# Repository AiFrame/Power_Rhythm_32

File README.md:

Power_Rhythm_32
===============

32 channels servo controller source code

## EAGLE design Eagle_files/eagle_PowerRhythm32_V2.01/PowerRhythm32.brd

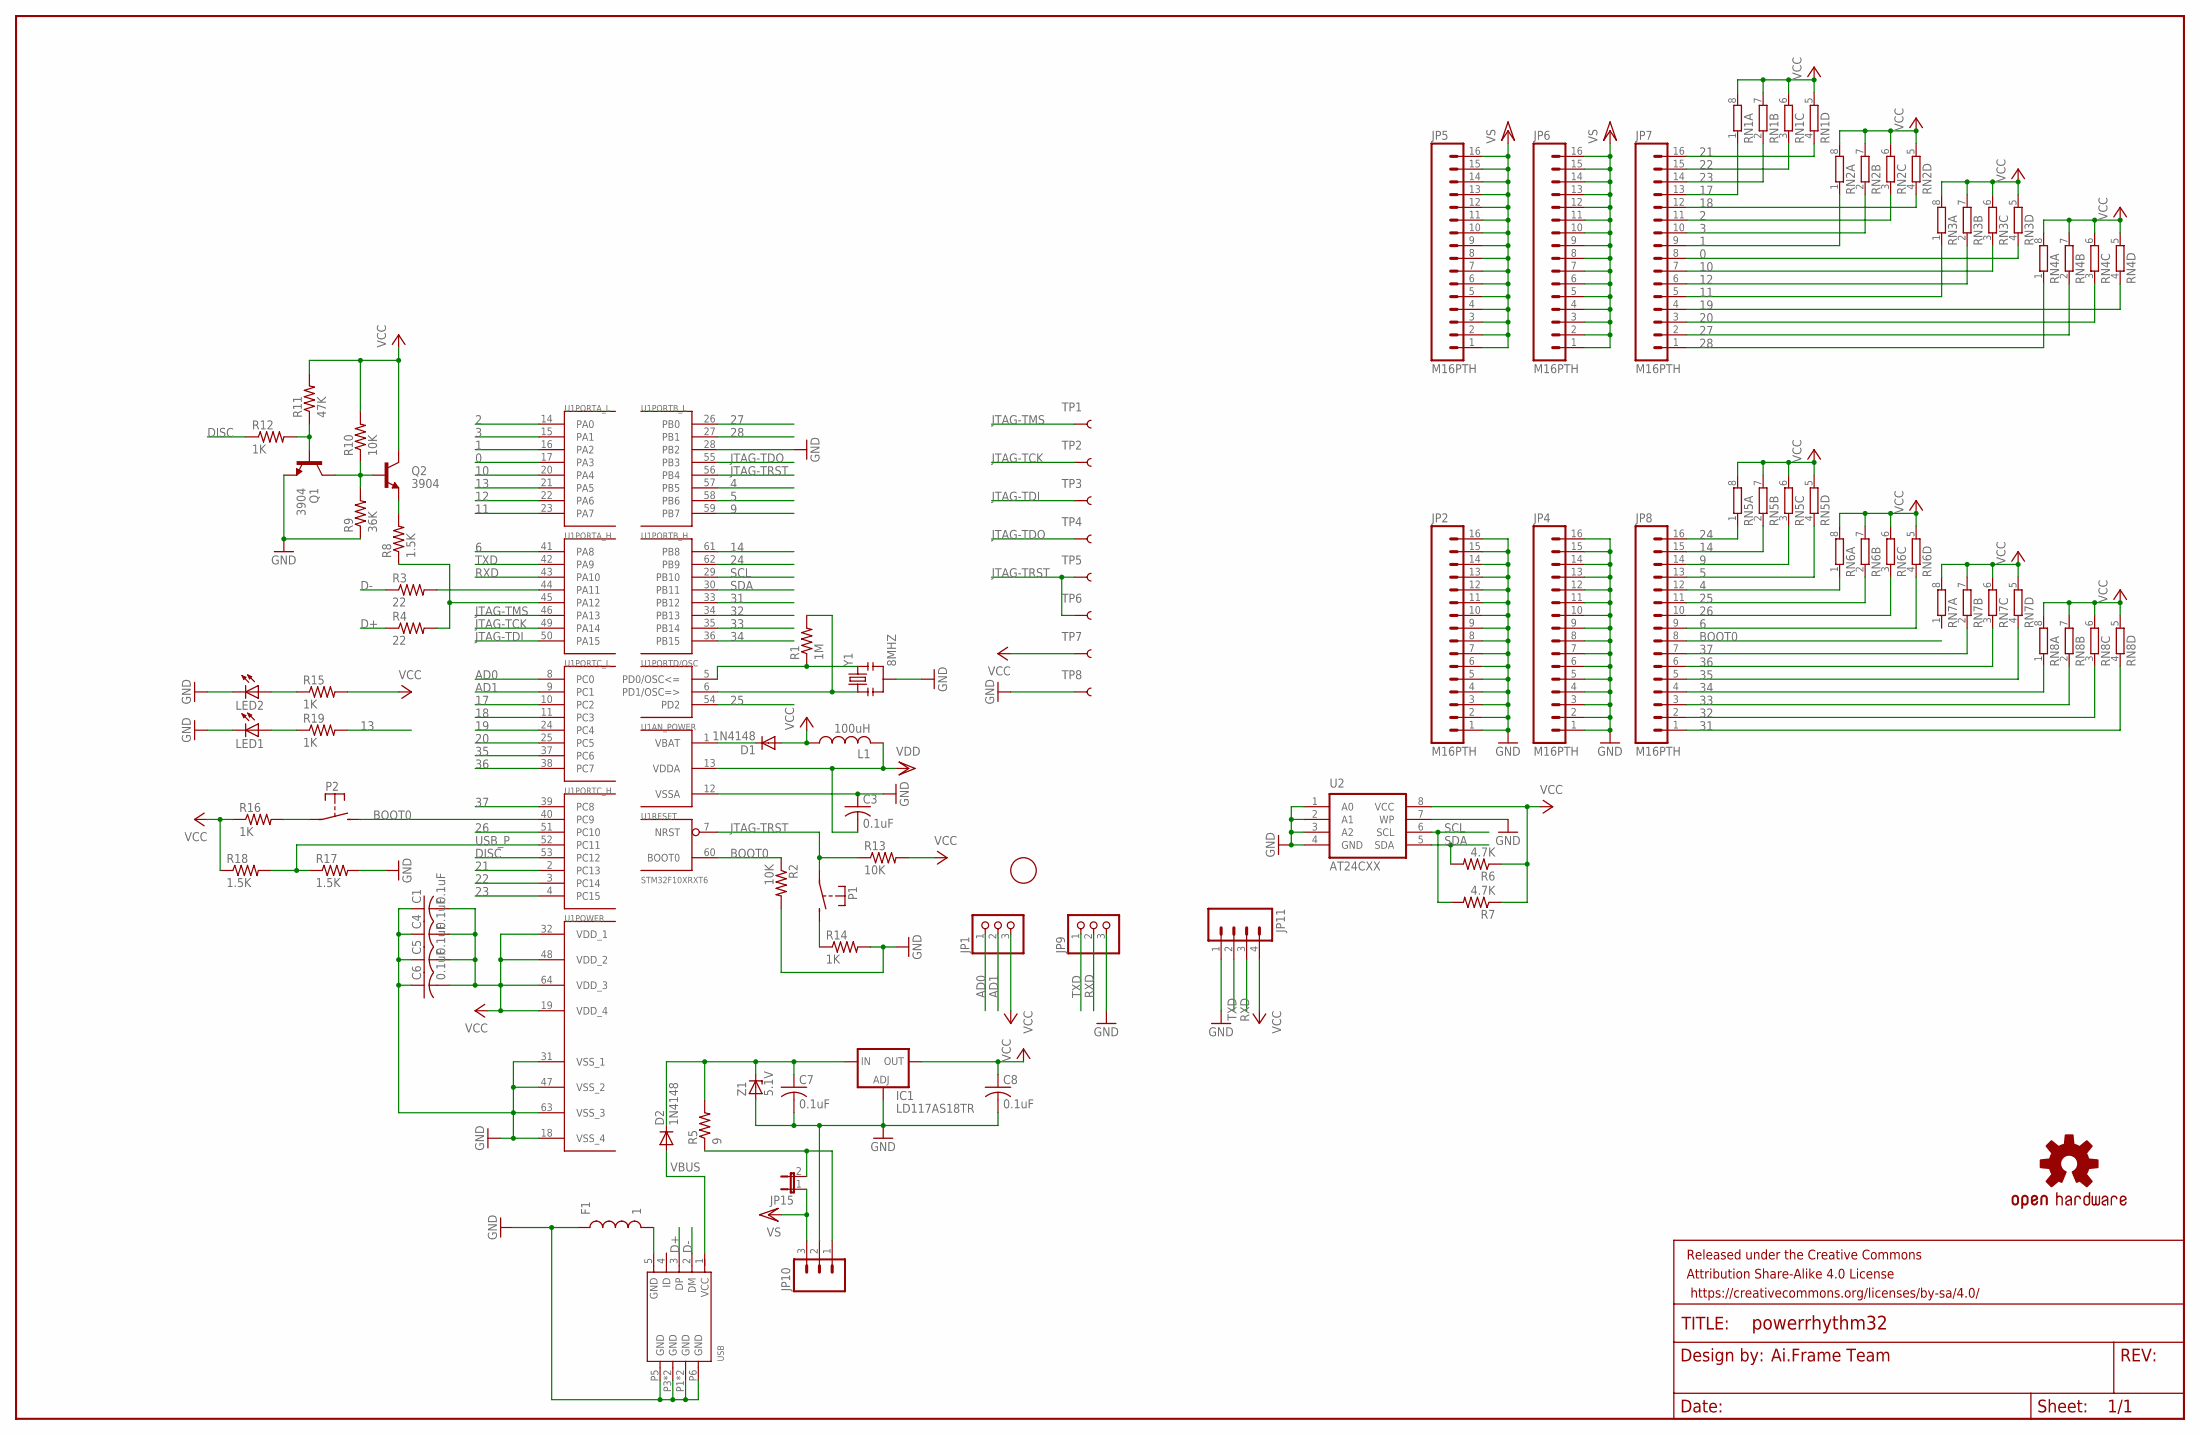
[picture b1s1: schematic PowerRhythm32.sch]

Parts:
C1, C3, C4, C5, C6, C7, C8: 0.1uF; C0603K
D1, D2: 1N4148; SOD123
F1: 1; 0805
FRAME1: FRAME-LEDGER; CREATIVE_COMMONS
IC1: LD117AS18TR; SOT223
JP1, JP9: PINHD-1X3; 1X03
JP2, JP4, JP5, JP6, JP7, JP8: M16PTH; 1X16
JP10: M03SCREW_LOCK; SCREWTERMINAL-3.5MM-3_LOCK.007S
JP11: M04PTH; 1X04
JP15: JUMPER-2PTH; 1X02
L1: 100uH; L2012C
LED1, LED2: LEDCHIP-LED0603; CHIP-LED0603
LOGO1: OSHW-LOGOS; OSHW-LOGO-S
P1, P2: TMAV433BAA
Q1, Q2: 3904; SOT23-3
R1: 1M; R0603
R2, R10, R13: 10K; R0603
R3, R4: 22; R0603
R5: 9; R1206
R6, R7: 4.7K; R0603
R8, R17, R18: 1.5K; R0603
R9: 36K; R0603
R11: 47K; R0603
R12, R14, R15, R16, R19: 1K; R0603
RN1, RN2, RN3, RN4, RN5, RN6, RN7, RN8: 4R-N0603-ARC; 0603-ARC
TP1, TP2, TP3, TP4, TP5, TP6, TP7, TP8: TEST-POINT3X5; PAD.03X.05
U1: STM32F10XRXT6; TQFP64
U2: AT24CXX; SO08-8S1
U$1: FIDUCIAL; FIDUCIAL_1MM
USB: MICRO-USB5+4P'5+6P'; MICRO-USB5+6P-SMD-0.65-AB
Y1: 8MHZ; RESONATOR-SMD
Z1: 5.1V; SOD80C

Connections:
0: JP7.8, RN3.4 (1), U1.17 (PA3)
1: JP7.9, RN2.1, U1.16 (PA2)
2: JP7.11, RN2.3 (1), U1.14 (PA0)
3: JP7.10, RN2.2 (1), U1.15 (PA1)
4: JP8.12, RN6.1, U1.57 (PB5)
5: JP8.13, RN5.4 (1), U1.58 (PB6)
6: JP8.9, RN6.4 (1), U1.41 (PA8)
9: JP8.14, RN5.3 (1), U1.59 (PB7)
10: JP7.7, RN3.3 (1), U1.20 (PA4)
11: JP7.5, RN3.1, U1.23 (PA7)
12: JP7.6, RN3.2 (1), U1.22 (PA6)
13: R19.2, U1.21 (PA5)
14: JP8.15, RN5.2 (1), U1.61 (PB8)
17: JP7.13, RN1.1, U1.10 (PC2)
18: JP7.12, RN2.4 (1), U1.11 (PC3)
19: JP7.4, RN4.4 (1), U1.24 (PC4)
20: JP7.3, RN4.3 (1), U1.25 (PC5)
21: JP7.16, RN1.4 (1), U1.2 (PC13)
22: JP7.15, RN1.3 (1), U1.3 (PC14)
23: JP7.14, RN1.2 (1), U1.4 (PC15)
24: JP8.16, RN5.1, U1.62 (PB9)
25: JP8.11, RN6.2 (1), U1.54 (PD2)
26: JP8.10, RN6.3 (1), U1.51 (PC10)
27: JP7.2, RN4.2 (1), U1.26 (PB0)
28: JP7.1, RN4.1, U1.27 (PB1)
31: JP8.1, RN8.4 (1), U1.33 (PB12)
32: JP8.2, RN8.3 (1), U1.34 (PB13)
33: JP8.3, RN8.2 (1), U1.35 (PB14)
34: JP8.4, RN8.1, U1.36 (PB15)
35: JP8.5, RN7.4 (1), U1.37 (PC6)
36: JP8.6, RN7.3 (1), U1.38 (PC7)
37: JP8.7, RN7.2 (1), U1.39 (PC8)
AD0: JP1.1, U1.8 (PC0)
AD1: JP1.2, U1.9 (PC1)
BOOT0: JP8.8, P2.P$2 (S), R2.1, U1.40 (PC9), U1.60 (BOOT0)
D+: R4.1, USB.3 (DP)
D-: R3.1, USB.2 (DM)
DISC: R12.1, U1.53 (PC12)
GND: C1.1, C3.1, C4.1, C5.1, C6.1, C7.2, C8.2, F1.1, IC1.1 (ADJ), JP2.1, JP2.2, JP2.3, JP2.4, JP2.5, JP2.6, JP2.7, JP2.8, JP2.9, JP2.10, JP2.11, JP2.12, JP2.13, JP2.14, JP2.15, JP2.16, JP4.1, JP4.2, JP4.3, JP4.4, JP4.5, JP4.6, JP4.7, JP4.8, JP4.9, JP4.10, JP4.11, JP4.12, JP4.13, JP4.14, JP4.15, JP4.16, JP9.3, JP10.2, JP11.1, LED1.C, LED2.C, Q1.2 (E), R2.2, R9.1, R14.2, R17.2, TP8.P$1, U1.12 (VSSA), U1.18 (VSS_4), U1.28 (PB2), U1.31 (VSS_1), U1.47 (VSS_2), U1.63 (VSS_3), U2.1 (A0), U2.2 (A1), U2.3 (A2), U2.4 (GND), U2.7 (WP), USB.P1 (GND), USB.P2 (GND), USB.P3 (GND), USB.P4 (GND), USB.P5 (GND), USB.P6 (GND), Y1.2, Z1.A
JTAG-TCK: TP2.P$1, U1.49 (PA14)
JTAG-TDI: TP3.P$1, U1.50 (PA15)
JTAG-TDO: TP4.P$1, U1.55 (PB3)
JTAG-TMS: TP1.P$1, U1.46 (PA13)
JTAG-TRST: P1.P$1, R13.1, TP5.P$1, TP6.P$1, U1.7 (NRST), U1.56 (PB4)
unnamed: R1.2, U1.6 (PD1/OSC=>), Y1.1
unnamed: D1.C, U1.1 (VBAT)
unnamed: LED2.A, R15.1
unnamed: R4.2, R8.1, U1.45 (PA12)
unnamed: JP10.1, JP15.2, R5.1
unnamed: R1.1, U1.5 (PD0/OSC<=), Y1.3
unnamed: R3.2, U1.44 (PA11)
unnamed: C7.1, D2.C, IC1.3 (IN), R5.2, Z1.C
unnamed: LED1.A, R19.1
unnamed: F1.2, USB.5 (GND)
unnamed: Q1.3 (C), Q2.1 (B), R9.2, R10.1
unnamed: P1.P$2 (S), R14.1
unnamed: Q2.2 (E), R8.2
unnamed: Q1.1 (B), R11.1, R12.2
unnamed: P2.P$1, R16.2
RXD: JP9.2, JP11.3, U1.43 (PA10)
SCL: R7.2, U1.29 (PB10), U2.6 (SCL)
SDA: R6.2, U1.30 (PB11), U2.5 (SDA)
TXD: JP9.1, JP11.2, U1.42 (PA9)
USB_P: R17.1, R18.2, U1.52 (PC11)
VBUS: D2.A, USB.1 (VCC)
VCC: C1.2, C4.2, C5.2, C6.2, C8.1, D1.A, IC1.4 (OUT), JP1.3, JP11.4, L1.1, Q2.3 (C), R6.1, R7.1, R10.2, R11.2, R13.2, R15.2, R16.1, R18.1, RN1.5 (2), RN1.6 (2), RN1.7 (2), RN1.8 (2), RN2.5 (2), RN2.6 (2), RN2.7 (2), RN2.8 (2), RN3.5 (2), RN3.6 (2), RN3.7 (2), RN3.8 (2), RN4.5 (2), RN4.6 (2), RN4.7 (2), RN4.8 (2), RN5.5 (2), RN5.6 (2), RN5.7 (2), RN5.8 (2), RN6.5 (2), RN6.6 (2), RN6.7 (2), RN6.8 (2), RN7.5 (2), RN7.6 (2), RN7.7 (2), RN7.8 (2), RN8.5 (2), RN8.6 (2), RN8.7 (2), RN8.8 (2), TP7.P$1, U1.19 (VDD_4), U1.32 (VDD_1), U1.48 (VDD_2), U1.64 (VDD_3), U2.8 (VCC)
VCC/2: JP5.1, JP5.2, JP5.3, JP5.4, JP5.5, JP5.6, JP5.7, JP5.8, JP5.9, JP5.10, JP5.11, JP5.12, JP5.13, JP5.14, JP5.15, JP5.16, JP6.1, JP6.2, JP6.3, JP6.4, JP6.5, JP6.6, JP6.7, JP6.8, JP6.9, JP6.10, JP6.11, JP6.12, JP6.13, JP6.14, JP6.15, JP6.16, JP10.3, JP15.1
VDD: C3.2, L1.2, U1.13 (VDDA)

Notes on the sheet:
Ai.Frame Team

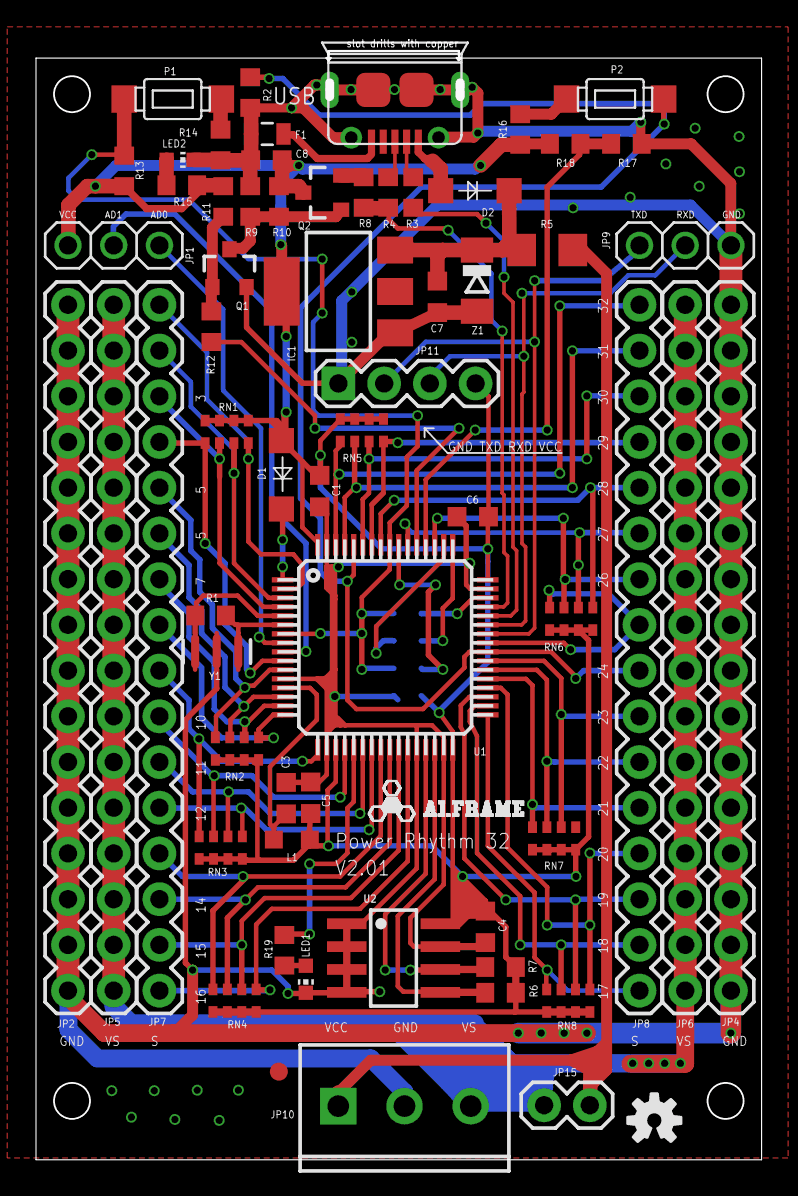
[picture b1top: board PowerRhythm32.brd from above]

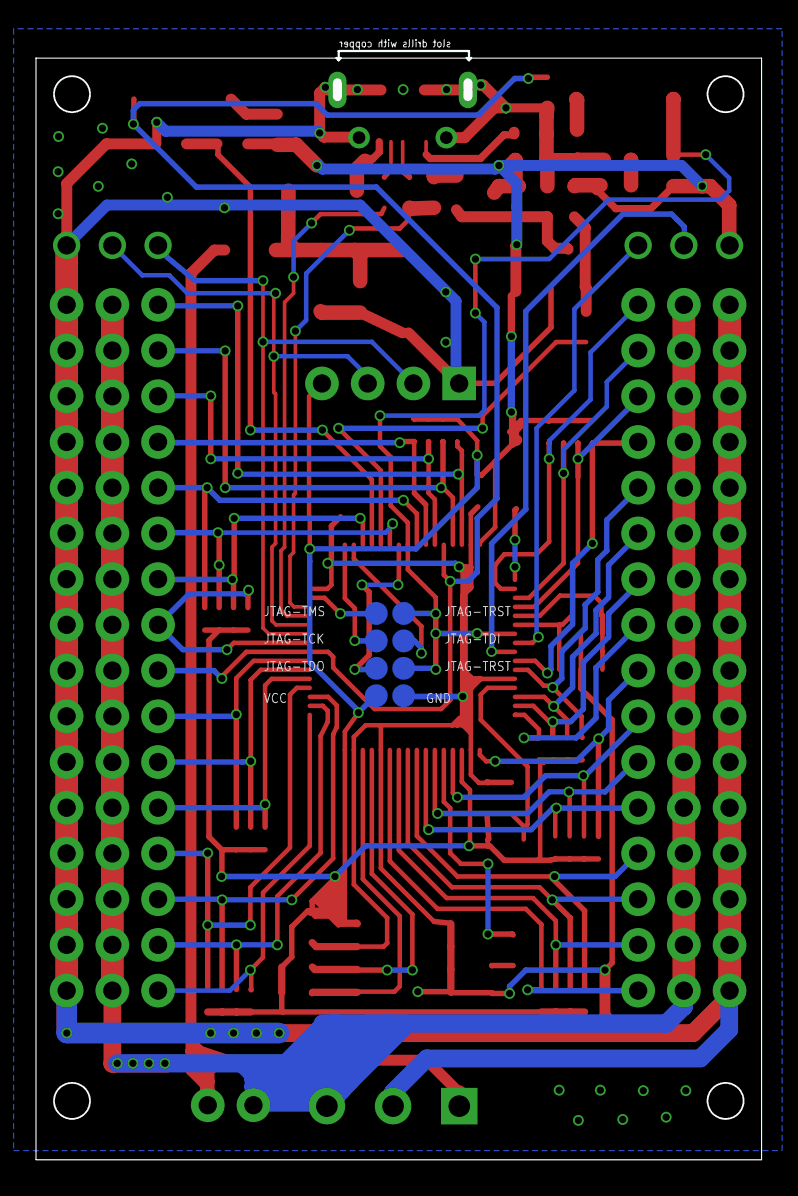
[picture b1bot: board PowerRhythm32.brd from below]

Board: 2 copper layers, 39.8 x 61.9 mm, 72 parts (8 on the bottom side), 68 nets.

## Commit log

2014-12-05 upload power_rhythm_32_Maple
    source code for the Maple REV 3
2014-12-05 eagle files upload
2014-12-11 update pdf
2014-12-13 Edit font
2014-12-14 Update connection for robots
2015-08-26 PCB update
    Update the USB design.
2015-08-26 Code update
    Change the way saving data from usb to flash, must work with the new APP
    for windows or Andriod.
2015-10-11 power_rhythm_32_Maple V1.3
    Add a time out mode for PWM output, when there is not command from uart
    or USB, the controller will shut down the PWM output in 5 seconds.
2015-10-11 power_rhythm_32_Maple_Firmware_V1.2
    Add a time out mode for PWM output, when there is not command from USB
    or UART, the controller with shut down the PWM output for saving battery
    in 5 seconeds
2015-10-11 V1.2
    V1.2
2015-10-11 power_rhythm_32_Maple_Firmware_V1.2
    ADD WATCH DOG
2015-10-15 V1.2
    Time out mode
2015-10-21 Update v1.2
    Update v1.2
2015-11-02 1.2
    BATTERY CHECK MOD
2015-11-09 ADD TESTING MOD
2016-05-06 Update Chinese manual

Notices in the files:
parts and their libraries:
memory-atmel: Copyright (C) 2008, Bob Starr
SparkFun-Connectors: Licensing: Creative Commons ShareAlike 4.0 International - https://creativecommons.org/licenses/by-sa/4.0
SparkFun-Aesthetics: Released under the Creative Commons Attribution Share-Alike 4.0 License
